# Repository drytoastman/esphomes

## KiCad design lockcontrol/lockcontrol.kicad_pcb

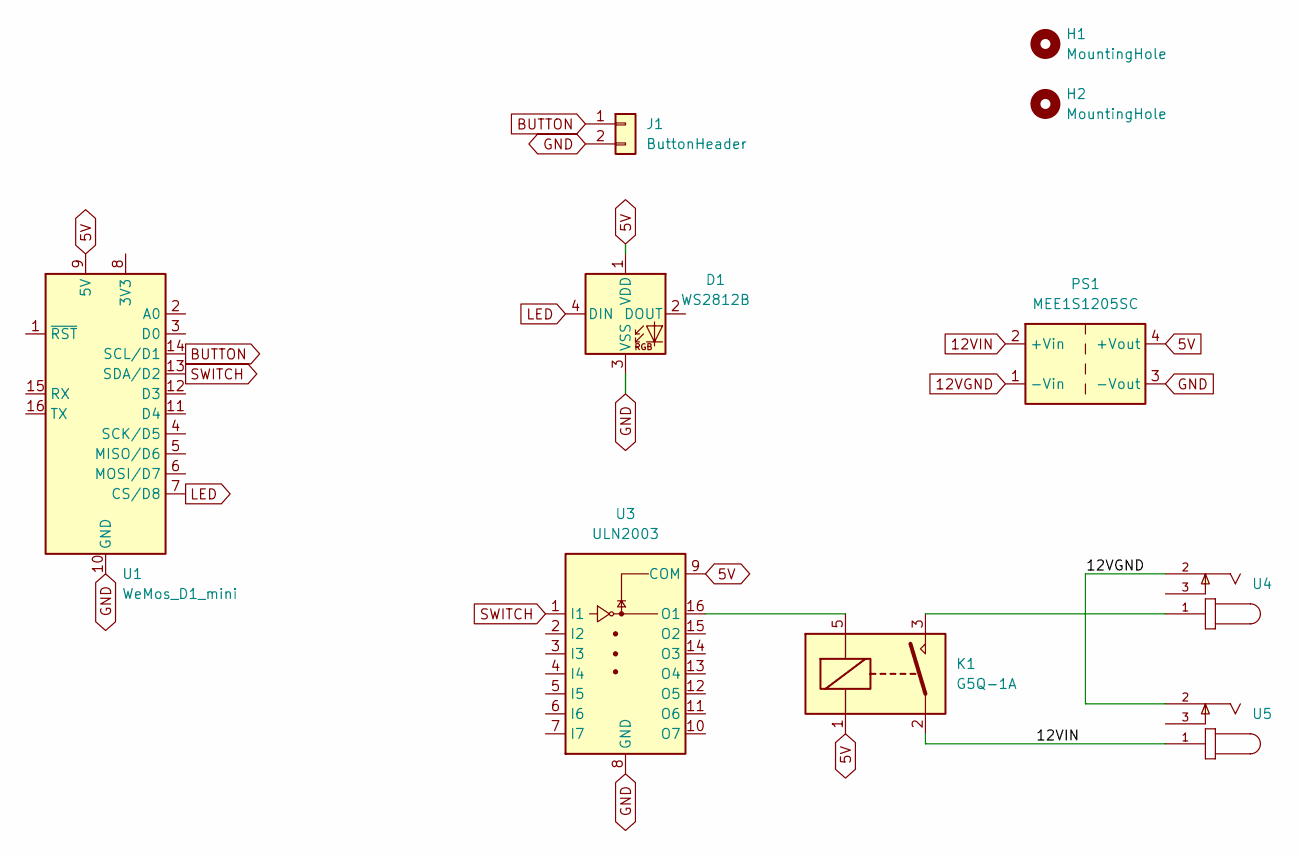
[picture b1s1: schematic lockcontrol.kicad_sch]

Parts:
D1: WS2812B; LED_WS2812B_PLCC4_5.0x5.0mm_P3.2mm
H1, H2: MountingHole; MountingHole_2.1mm
J1: ButtonHeader; PinHeader_1x02_P2.54mm_Vertical
K1: G5Q-1A; Relay_SPST_Omron-G5Q-1A
PS1: MEE1S1205SC; Converter_DCDC_Murata_MEE1SxxxxSC_THT
U1: WeMos_D1_mini; WEMOS_D1_mini_light
U3: ULN2003; SOIC-16_3.9x9.9mm_P1.27mm
U4, U5: Barrel_Jack_Switch; CUI_PJ-002AH

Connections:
5V: D1.1 (VDD), K1.1, PS1.4 (+Vout), U1.9 (5V), U3.9 (COM)
12VGND: PS1.1 (-Vin), U4.2, U5.2
12VIN: K1.2, PS1.2 (+Vin), U5.1
BUTTON: J1.1, U1.14 (SCL/D1)
GND: D1.3 (VSS), J1.2, PS1.3 (-Vout), U1.10 (GND), U3.8 (GND)
LED: D1.4 (DIN), U1.7 (CS/D8)
unnamed: K1.3, U4.1
unnamed: K1.5, U3.16 (O1)
SWITCH: U1.13 (SDA/D2), U3.1 (I1)

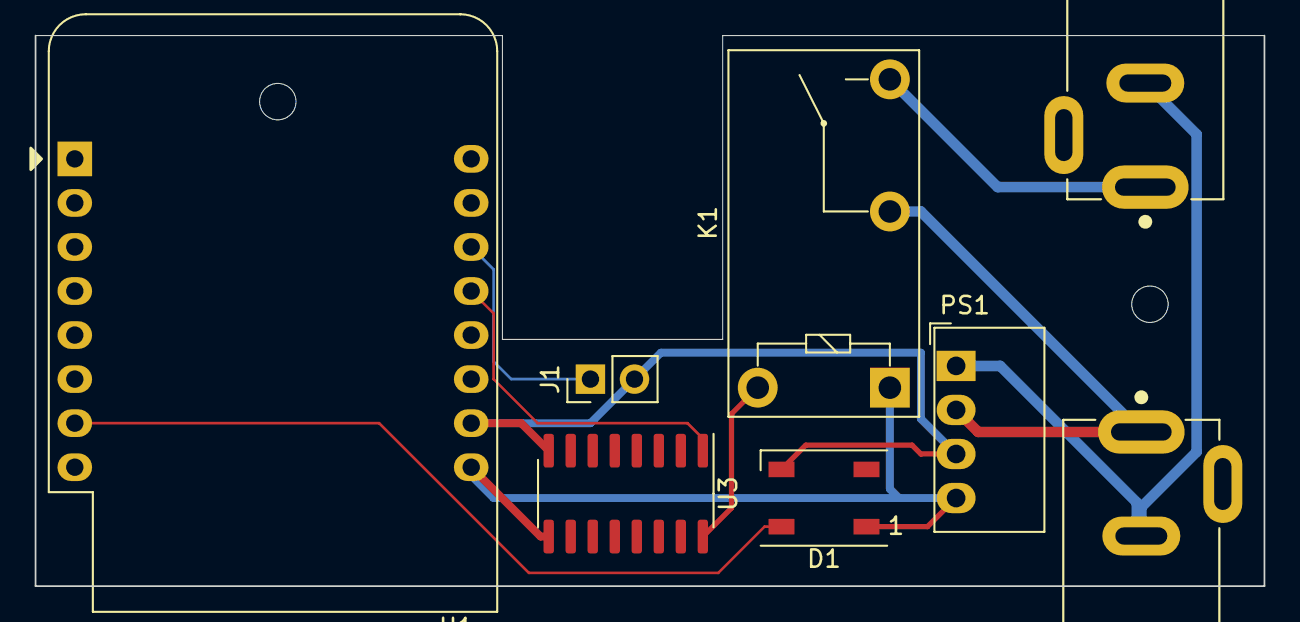
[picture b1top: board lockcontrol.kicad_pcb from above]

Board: 2 copper layers, 70.9 x 31.8 mm, 10 parts (0 on the bottom side), 9 nets.

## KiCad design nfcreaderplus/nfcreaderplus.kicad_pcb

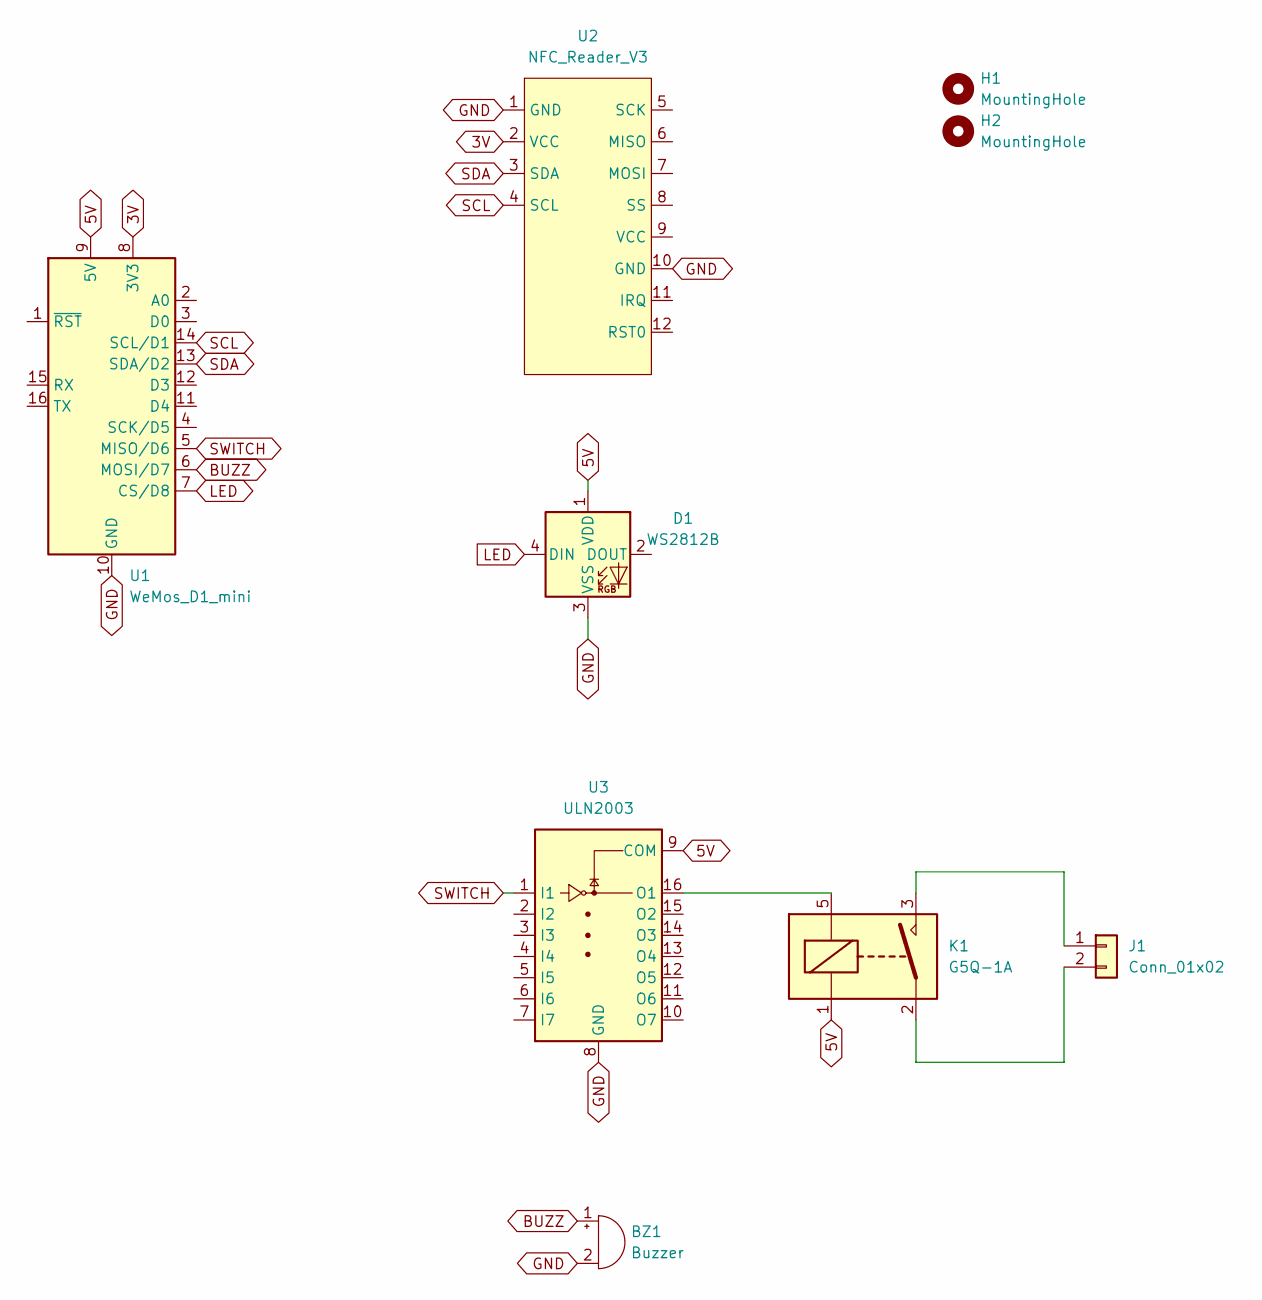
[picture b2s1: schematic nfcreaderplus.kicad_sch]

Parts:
BZ1: Buzzer; CUI_CPT-9019S-SMT
D1: WS2812B; LED_WS2812B_PLCC4_5.0x5.0mm_P3.2mm
H1, H2: MountingHole; MountingHole_2.1mm
J1: Conn_01x02; PinHeader_1x02_P2.54mm_Vertical
K1: G5Q-1A; Relay_SPST_Omron-G5Q-1A
U1: WeMos_D1_mini; WEMOS_D1_mini_light
U2: NFC_Reader_V3
U3: ULN2003; SOIC-16_3.9x9.9mm_P1.27mm

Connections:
3V: U1.8 (3V3), U2.2 (VCC)
5V: D1.1 (VDD), K1.1, U1.9 (5V), U3.9 (COM)
BUZZ: BZ1.1 (-), U1.6 (MOSI/D7)
GND: BZ1.2 (+), D1.3 (VSS), U1.10 (GND), U2.1 (GND), U2.10 (GND), U3.8 (GND)
LED: D1.4 (DIN), U1.7 (CS/D8)
unnamed: J1.1, K1.3
unnamed: J1.2, K1.2
unnamed: K1.5, U3.16 (O1)
SCL: U1.14 (SCL/D1), U2.4 (SCL)
SDA: U1.13 (SDA/D2), U2.3 (SDA)
SWITCH: U1.5 (MISO/D6), U3.1 (I1)

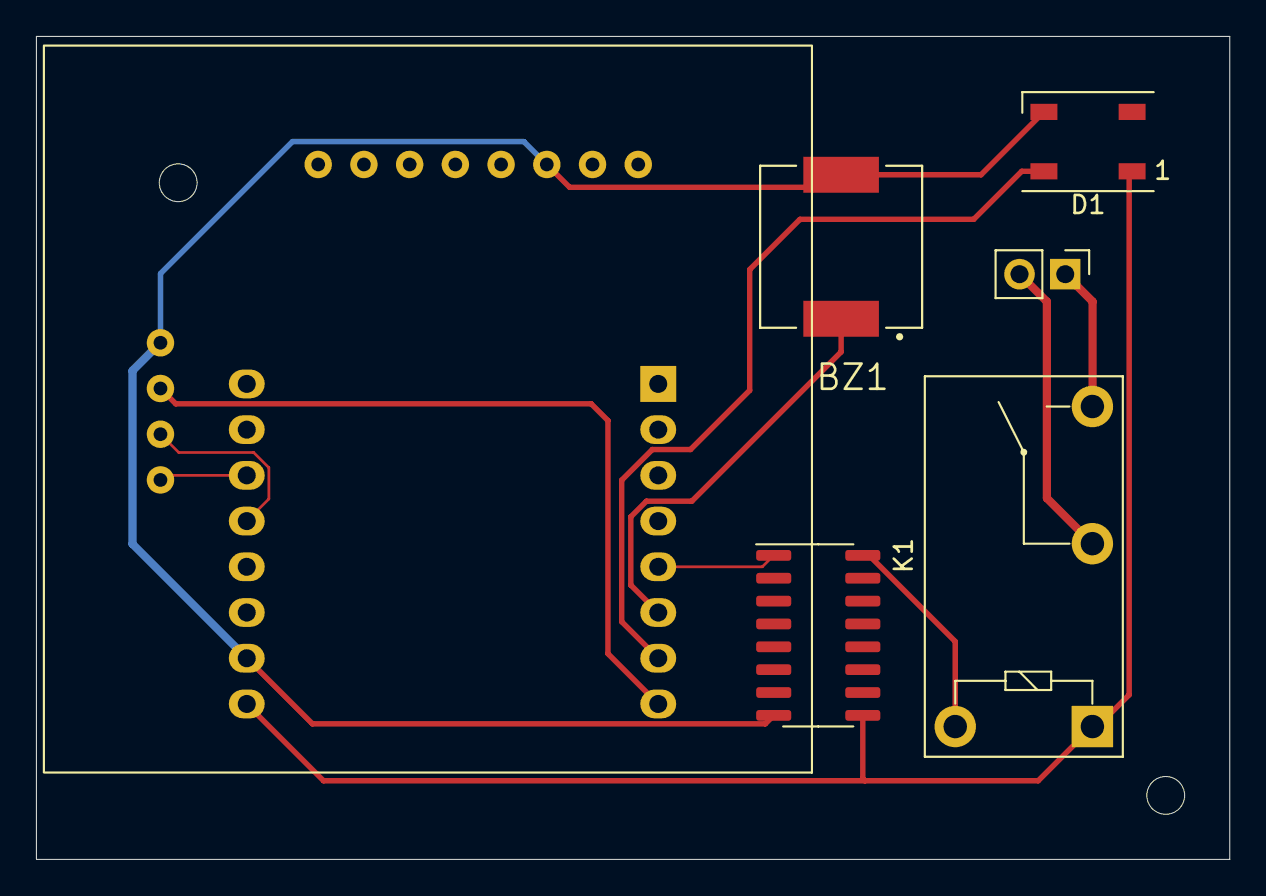
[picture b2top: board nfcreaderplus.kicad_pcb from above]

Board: 2 copper layers, 66.3 x 45.7 mm, 9 parts (1 on the bottom side), 11 nets.

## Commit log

2022-11-15 v1 hardware and starting yaml files
2022-11-17 share libs
2022-11-17 update lock control footprints and esp pins
2022-11-17 rename to plus
2022-11-17 the simpler nfc reader
2022-11-19 updates to reader
2022-11-19 add mounting holes
2022-11-22 central place to set led home value, add variable as we may allow adjustments later
2022-11-22 mounting holes
2022-11-23 esp updates
2022-11-30 add led yellow after boot, make for more resiliant i2c bus
2022-11-30 relay driver is grounding, pass 5V through relay then
2025-03-07 capture before removing disk
